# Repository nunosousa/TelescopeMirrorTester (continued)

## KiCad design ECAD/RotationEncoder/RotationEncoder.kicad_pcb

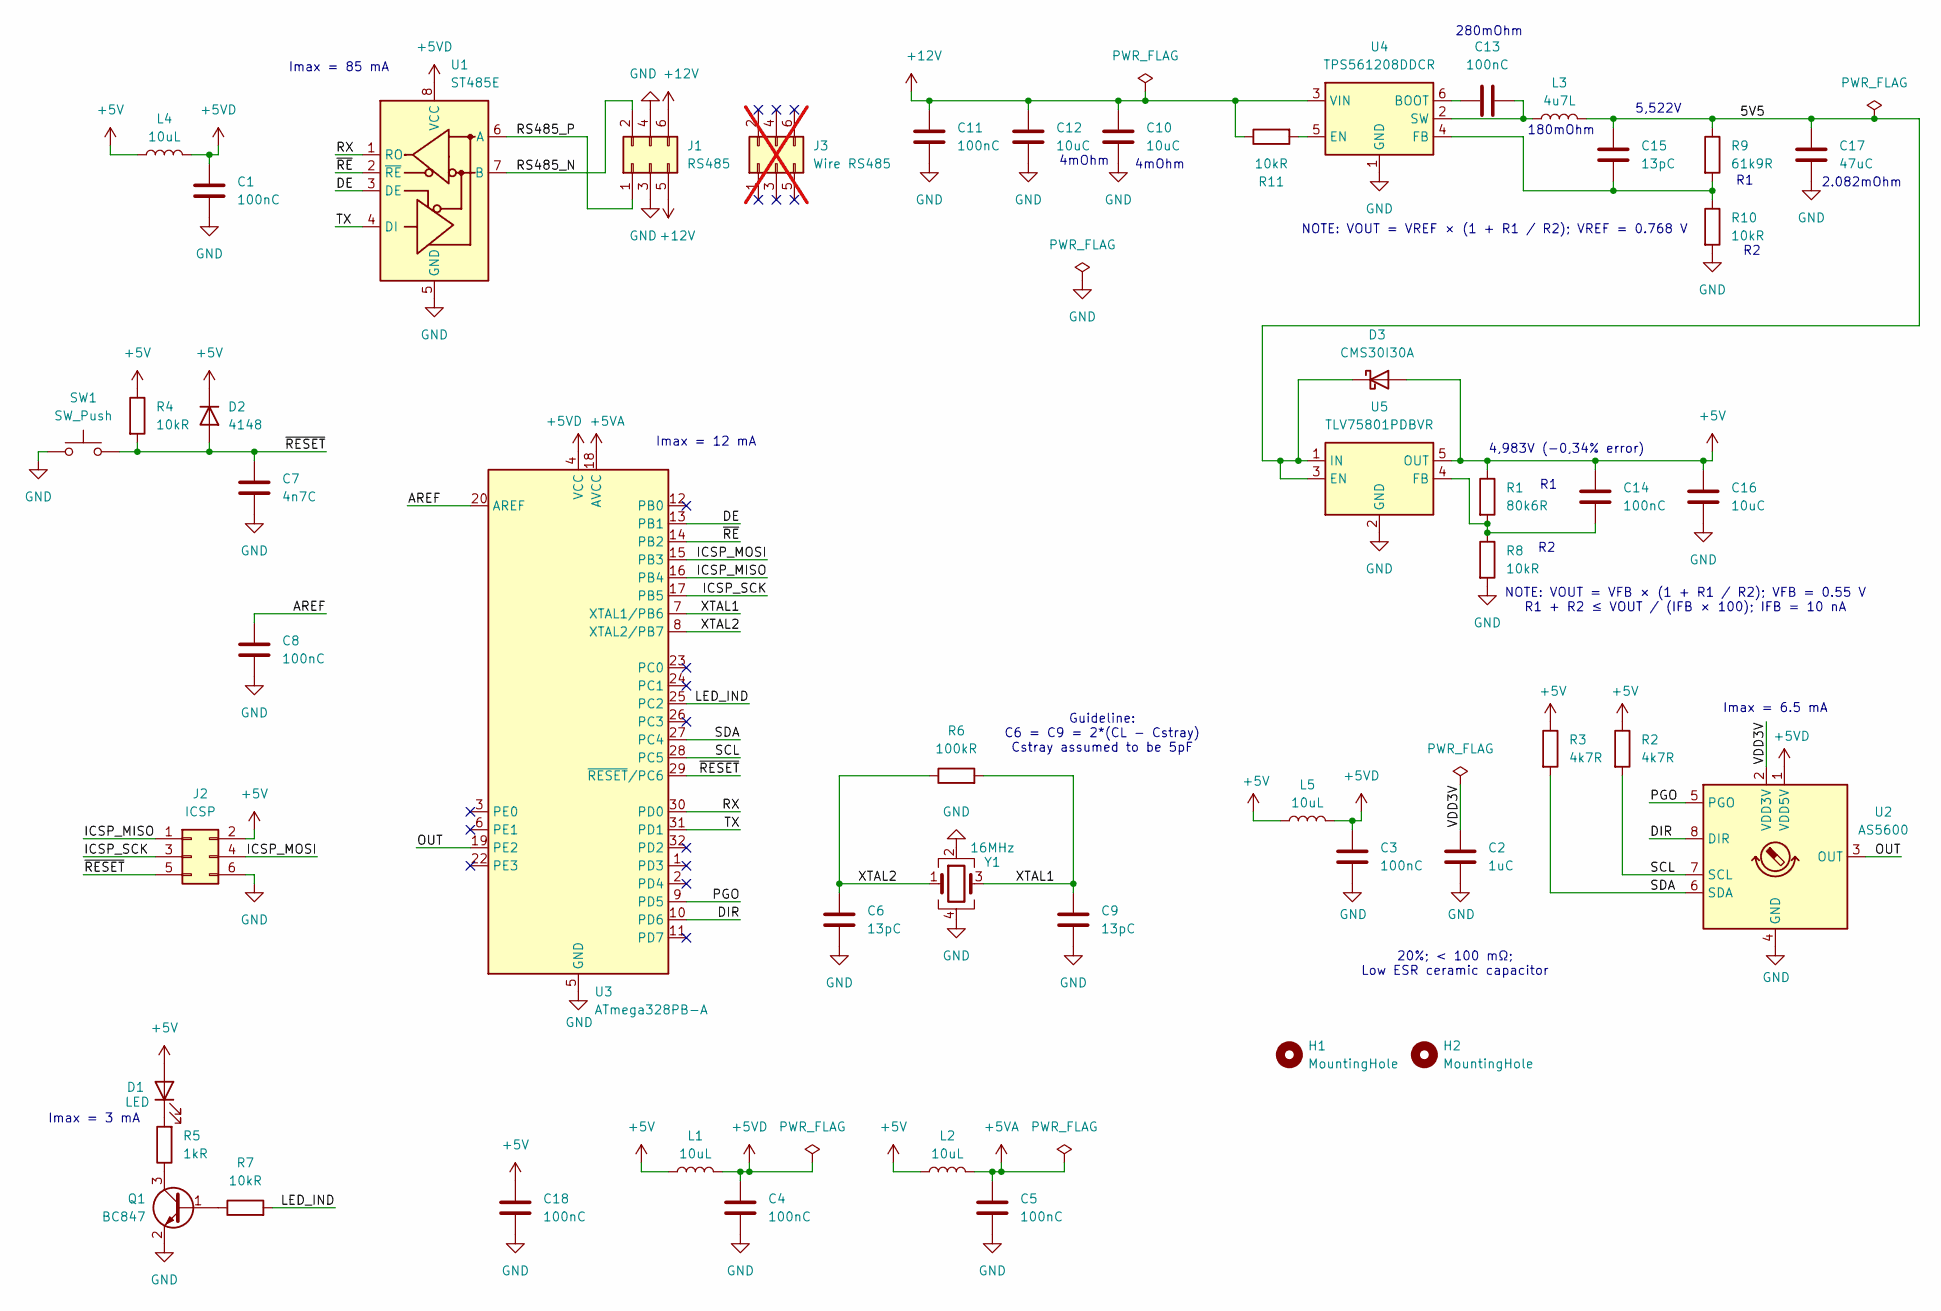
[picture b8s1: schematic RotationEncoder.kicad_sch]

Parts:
C1, C3, C4, C5, C8, C11, C13, C14, C18: 100nC; C_0805_2012Metric; MPN C0805F104K5RACAUTO
C2: 1uC; C_0805_2012Metric; MPN CL21B105KAFNNNE
C6, C9, C15: 13pC; C_0805_2012Metric; MPN 0805CG130J500NT
C7: 4n7C; C_0805_2012Metric; MPN CC0805JRX7R9BB472
C10, C12, C16: 10uC; C_0805_2012Metric; MPN GRM21BR61E106MA73L
C17: 47uC; C_1210_3225Metric; MPN GRM32ER61C476KE15L
D1: LED; LED_0805_2012Metric; MPN LTST-C171KGKT
D2: 4148; D_SOD-123; MPN MMSD4148T1G
D3: CMS30I30A; D_SOD-128; MPN CMS30I30A(TE12L,QM
H1, H2: MountingHole; MountingHole_3.2mm_M3
J1: RS485; IDC-Header_2x03_P2.54mm_Vertical; MPN HC-JN254-2-03-Z
J2: ICSP; PinHeader_2x03_P2.54mm_Vertical; MPN PZ254-2-03-Z-8.5
J3: Wire RS485; IDC-Header_2x03_P2.54mm_Vertical; MPN I254-2*3-G-3-B; not fitted
L1, L2, L4, L5: 10uL; L_0805_2012Metric; MPN LQM21FN100M80L
L3: 4u7L; L_1008_2520Metric; MPN LQM2HPN4R7MG0L
Q1: BC847; SOT-23; MPN BC847C,215
R1: 80k6R; R_0805_2012Metric; MPN RT0805BRD0780K6L
R2, R3: 4k7R; R_0805_2012Metric; MPN RC0805JR-074K7L
R4, R7, R11: 10kR; R_0805_2012Metric; MPN RC0805JR-0710KL
R5: 1kR; R_0805_2012Metric; MPN RC0805FR-071KL
R6: 100kR; R_0805_2012Metric; MPN RT0805BRD07100KL
R8, R10: 10kR; R_0805_2012Metric; MPN RT0805BRD0710KL
R9: 61k9R; R_0805_2012Metric; MPN PTFR0805B61K9P9
SW1: SW_Push; SW_Push_1P1T_XKB_TS-1187A; MPN TS-1187A-C-E-B
U1: ST485E; SOIC-8_3.9x4.9mm_P1.27mm; MPN ST485EBDR
U2: AS5600; SOIC-8_3.9x4.9mm_P1.27mm; MPN AS5600-ASOT
U3: ATmega328PB-A; TQFP-32_7x7mm_P0.8mm; MPN ATMEGA328PB-AU
U4: TPS561208DDCR; SOT-23-6; MPN TPS561208DDCR
U5: TLV75801PDBVR; SOT-23-5; MPN TLV75801PDBVR
Y1: 16MHz; Crystal_SMD_3225-4Pin_3.2x2.5mm; MPN X1E0000210119

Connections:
+5V: C14.1, C16.1, C18.1, D1.2 (A), D2.1 (K), D3.2 (A), J2.2, L1.1, L2.1, L4.1, L5.1, R1.1, R2.1, R3.1, R4.1, U5.5 (OUT)
+5VA: C5.1, L2.2, U3.18 (AVCC)
+5VD: C1.1, C3.1, C4.1, L1.2, L4.2, L5.2, U1.8 (VCC), U2.1 (VDD5V), U3.4 (VCC)
+12V: C10.1, C11.2, C12.1, J1.5, J1.6, R11.1, U4.3 (VIN)
/5V5: C15.1, C17.1, D3.1 (K), L3.2, R9.1, U5.1 (IN), U5.3 (EN)
/AREF: C8.1, U3.20 (AREF)
/DE: U1.3 (DE), U3.13 (PB1)
/DIR: U2.8 (DIR), U3.10 (PD6)
/ICSP_MISO: J2.1, U3.16 (PB4)
/ICSP_MOSI: J2.4, U3.15 (PB3)
/ICSP_SCK: J2.3, U3.17 (PB5)
/LED_IND: R7.2, U3.25 (PC2)
/OUT: U2.3 (OUT), U3.19 (PE2)
/PGO: U2.5 (PGO), U3.9 (PD5)
/RS485_N: J1.2, U1.7 (B)
/RS485_P: J1.1, U1.6 (A)
/RX: U1.1 (RO), U3.30 (PD0)
/SCL: R2.2, U2.7 (SCL), U3.28 (PC5)
/SDA: R3.2, U2.6 (SDA), U3.27 (PC4)
/TX: U1.4 (DI), U3.31 (PD1)
/VDD3V: C2.1, U2.2 (VDD3V)
/XTAL1: C9.1, R6.2, U3.7 (XTAL1/PB6), Y1.3
/XTAL2: C6.1, R6.1, U3.8 (XTAL2/PB7), Y1.1
/~RESET: C7.1, D2.2 (A), J2.5, R4.2, SW1.2, U3.29 (~RESET/PC6)
/~RE: U1.2 (~RE), U3.14 (PB2)
GND: C1.2, C2.2, C3.2, C4.2, C5.2, C6.2, C7.2, C8.2, C9.2, C10.2, C11.1, C12.2, C16.2, C17.2, C18.2, J1.3, J1.4, J2.6, Q1.2 (E), R8.2, R10.2, SW1.1, U1.5 (GND), U2.4 (GND), U3.5 (GND), U3.21 (GND), U4.1 (GND), U5.2 (GND), Y1.2, Y1.4
unnamed: D1.1 (K), R5.2
unnamed: Q1.1 (B), R7.1
unnamed: Q1.3 (C), R5.1
unnamed: C13.1, U4.6 (BOOT)
unnamed: R11.2, U4.5 (EN)
unnamed: C15.2, R9.2, R10.1, U4.4 (FB)
unnamed: C13.2, L3.1, U4.2 (SW)
unnamed: C14.2, R1.2, R8.1, U5.4 (FB)

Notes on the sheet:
Imax = 12 mA
NOTE: VOUT = VREF × (1 + R1 / R2); VREF = 0.768 V
4mOhm
280mOhm
Imax = 6.5 mA
Imax = 85 mA
Imax = 3 mA
4,983V (-0,34% error)
180mOhm
NOTE: VOUT = VFB × (1 + R1 / R2); VFB = 0.55 V R1 + R2 ≤ VOUT / (IFB × 100); IFB = 10 nA
5,522V
2.082mOhm
20%; < 100 mΩ; Low ESR ceramic capacitor
Guideline: C6 = C9 = 2*(CL - Cstray) Cstray assumed to be 5pF

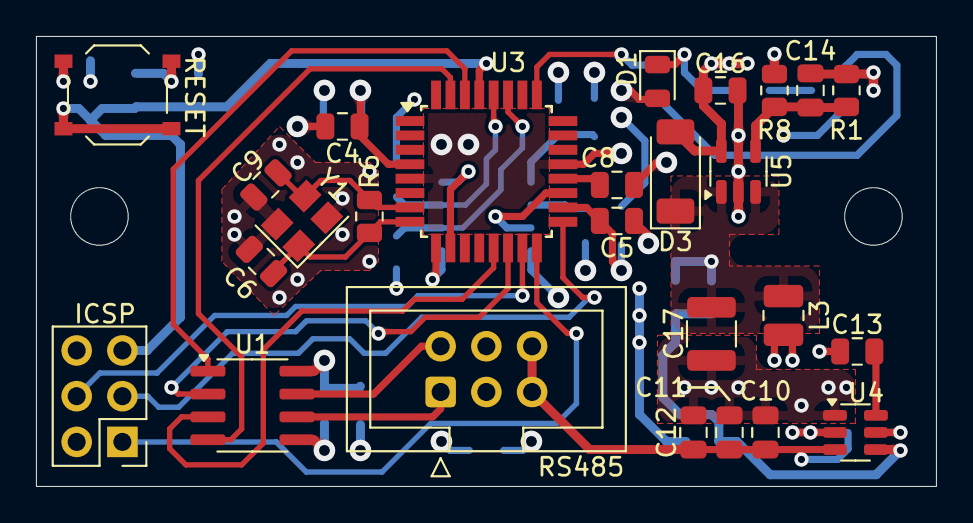
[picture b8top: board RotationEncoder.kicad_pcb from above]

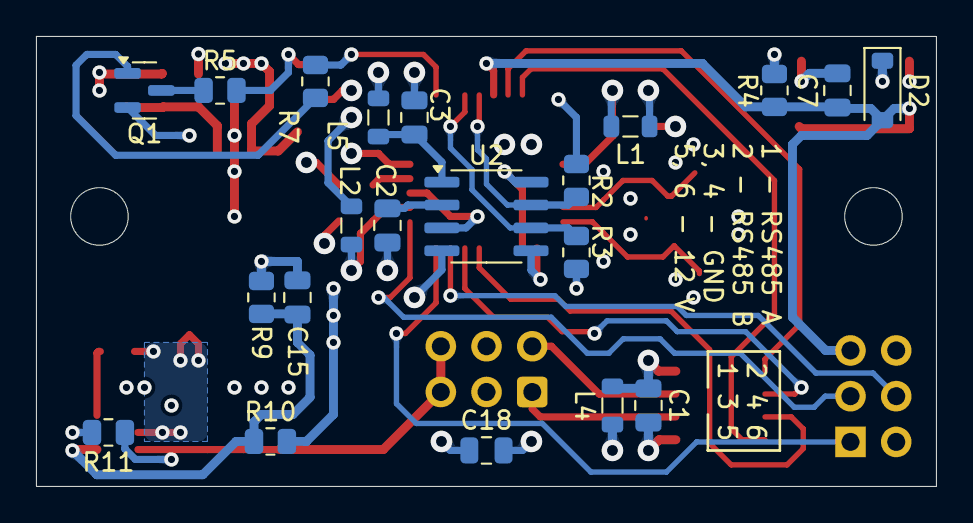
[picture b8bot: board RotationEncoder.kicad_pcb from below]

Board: 4 copper layers, 50.0 x 25.0 mm, 49 parts (21 on the bottom side), 34 nets.

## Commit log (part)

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2024-07-14 Progressed ECAD.
2024-08-15 Progressed ECAD
2024-09-14 Added Gerbers.
2024-09-14 Progressed CAD.
2025-03-09 Restored DataShield board original version.
2025-03-30 Added interactive boms.
2025-04-12 Generated Encoder Mount files.
2025-04-12 Minor improvements.
2025-04-12 Minor adjustments.
2025-04-12 Added new encoder support.
2025-04-13 Added new encoder mount.
2025-04-13 Progressed Encoder_KFL08.FCStd
2025-04-17 Progressed Encoder_Elevation_Plate.FCStd
2025-04-18 Progressed Elevation_Plate_Assembly.FCStd
2025-07-12 Added new BDCMotorControlShield board version
2025-07-13 Added BDCMotorControlShieldMega board
2025-08-05 Added NAND logic alternatives
2025-09-13 Added new board.
2026-01-20 Changed PCB to 90mm.
2026-04-01 Progress ECAD.
2026-04-23 Updated schematic from kicad version 9.0 to 10.0.
2026-05-09 Progresed ECAD.
2026-05-30 Motor Control Board Rev A
